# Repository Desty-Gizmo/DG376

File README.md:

# DG376

DG means "Desty Gizmo" or "Desty Gadget", a series of low power gadgets.

376: a random number I assign to name the model.

DG376V: using 10mm disk vibration motor (through-hole).
DG376R: using biased weight vibration motor (SMD).

# Counter

A counter that supports quick countdown function. Will notify the user when the time is up.

# MCU

STM32L010C6T6 $1.70 -> $1.67.  
STM32L011K4T6 $1.79 -> $1.68. Has symbol in KiCad

# Note

- Set GPIO to float before sleep.
-

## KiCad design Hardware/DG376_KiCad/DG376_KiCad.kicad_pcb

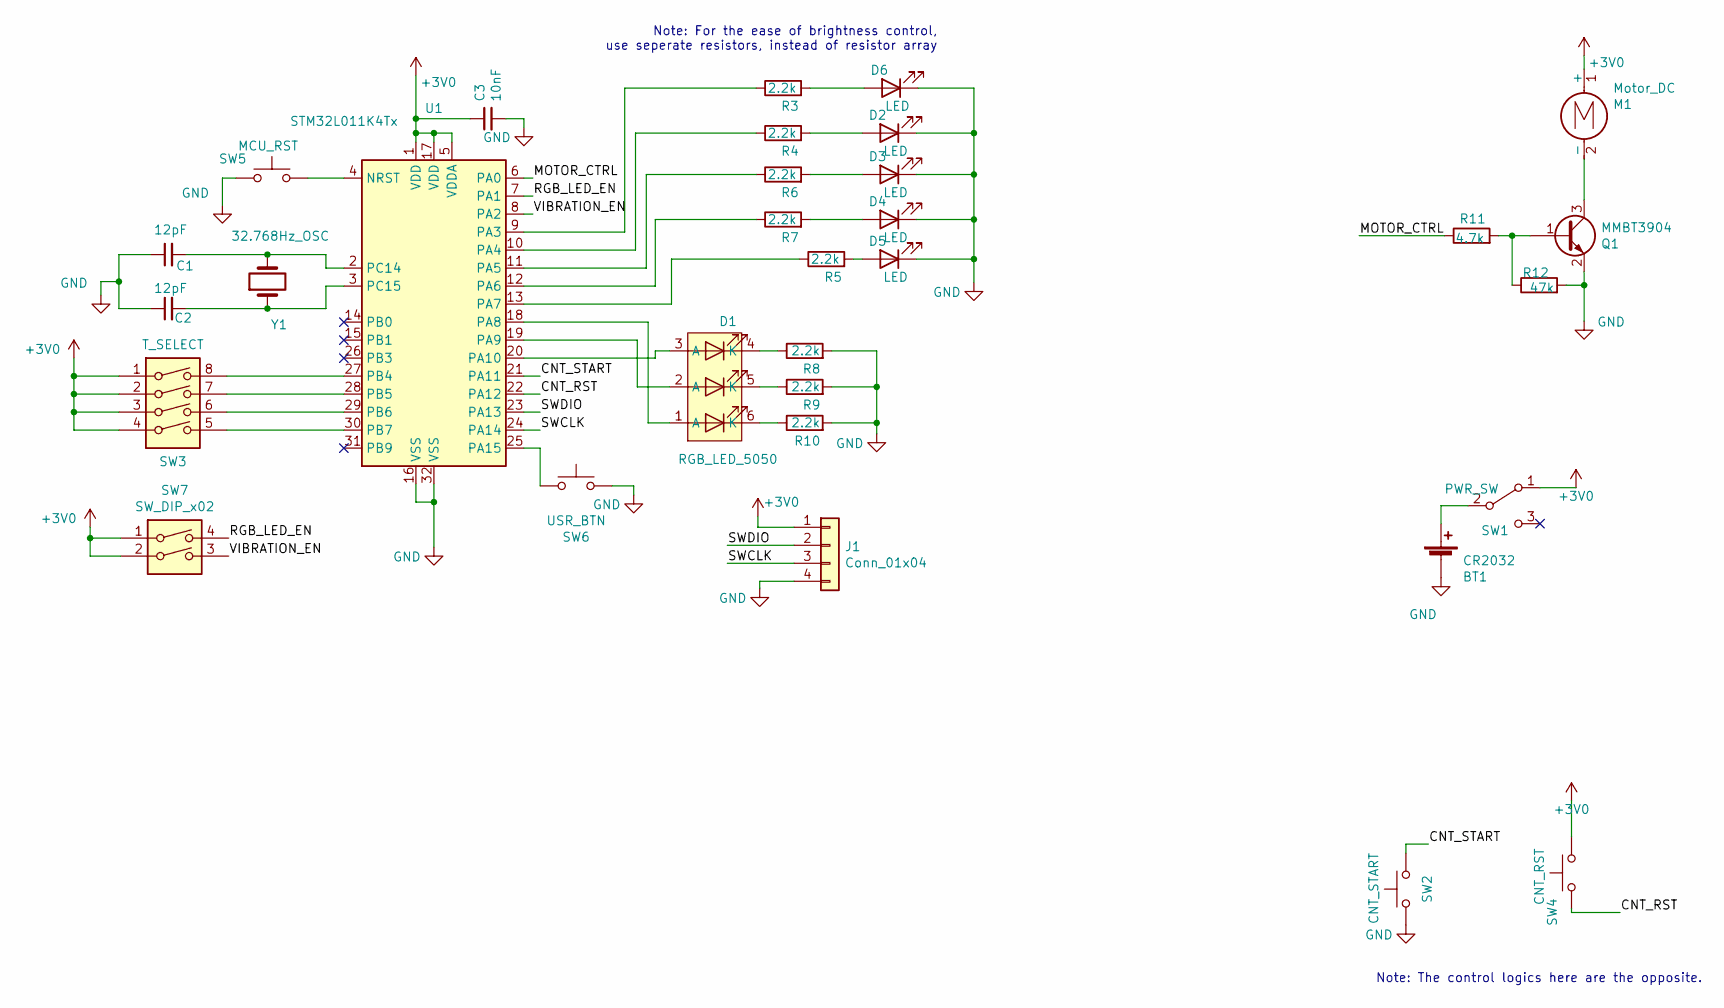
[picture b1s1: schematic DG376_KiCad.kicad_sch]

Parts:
BT1: CR2032; CR2032_Battery_Holder
C1, C2: 12pF; C_0603_1608Metric
C3: 10nF; C_0603_1608Metric
D1: RGB_LED_5050; LED_RGB_5050-6
D2, D3, D4, D5, D6: LED; LED_0603_1608Metric
J1: Conn_01x04; PinSocket_1x04_P1.27mm_Vertical
M1: Motor_DC; Vibration Motor 10mm
Q1: MMBT3904; SOT-23
R3, R4, R5, R6, R7, R8, R9, R10: 2.2k; R_0603_1608Metric
R11: 4.7k; R_0603_1608Metric
R12: 47k; R_0603_1608Metric
SW1: PWR_SW; Shouhan MSK12C02
SW2: CNT_START; Alps_SMD_Button_SKPMAPE010
SW3: T_SELECT; Diptronics DMR-04-V-TR
SW4: CNT_RST; Alps_SMD_Button_SKPMAPE010
SW5: MCU_RST; USAKRO UK-B0273-SP25Y
SW6: USR_BTN; USAKRO UK-B0273-SP25Y
SW7: SW_DIP_x02; Diptronics_SW_DIP_DHN-02-V-T-R
U1: STM32L011K4Tx; LQFP-32_7x7mm_P0.8mm
Y1: 32.768Hz_OSC; Crystal_SMD_3215-2Pin_3.2x1.5mm

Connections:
+3V0: C3.1, J1.1, M1.1 (+), SW1.1 (A), SW3.1, SW3.2, SW3.3, SW3.4, SW4.2, SW7.1, SW7.2, U1.1 (VDD), U1.5 (VDDA), U1.17 (VDD)
/CNT_RST: SW4.1, U1.22 (PA12)
/CNT_START: SW2.2, U1.21 (PA11)
/MOTOR_CTRL: R11.1, U1.6 (PA0)
/RGB_LED_EN: SW7.4, U1.7 (PA1)
/SWCLK: J1.3, U1.24 (PA14)
/SWDIO: J1.2, U1.23 (PA13)
/VIBRATION_EN: SW7.3, U1.8 (PA2)
GND: BT1.2 (-), C1.1, C2.1, C3.2, D2.1 (K), D3.1 (K), D4.1 (K), D5.1 (K), D6.1 (K), J1.4, Q1.2 (E), R8.2, R9.2, R10.2, R12.2, SW2.1, SW5.1, SW6.2, U1.16 (VSS), U1.32 (VSS)
unnamed: BT1.1 (+), SW1.2 (B)
unnamed: C1.2, U1.2 (PC14), Y1.2
unnamed: C2.2, U1.3 (PC15), Y1.1
unnamed: D1.1 (A), U1.18 (PA8)
unnamed: D1.2 (A), U1.19 (PA9)
unnamed: D1.3 (A), U1.20 (PA10)
unnamed: D1.4 (K), R8.1
unnamed: D1.5 (K), R9.1
unnamed: D1.6 (K), R10.1
unnamed: D2.2 (A), R4.2
unnamed: D3.2 (A), R6.2
unnamed: D4.2 (A), R7.2
unnamed: D5.2 (A), R5.2
unnamed: D6.2 (A), R3.2
unnamed: M1.2 (-), Q1.3 (C)
unnamed: Q1.1 (B), R11.2, R12.1
unnamed: R3.1, U1.9 (PA3)
unnamed: R4.1, U1.10 (PA4)
unnamed: R5.1, U1.13 (PA7)
unnamed: R6.1, U1.11 (PA5)
unnamed: R7.1, U1.12 (PA6)
unnamed: SW3.5, U1.30 (PB7)
unnamed: SW3.6, U1.29 (PB6)
unnamed: SW3.7, U1.28 (PB5)
unnamed: SW3.8, U1.27 (PB4)
unnamed: SW5.2, U1.4 (NRST)
unnamed: SW6.1, U1.25 (PA15)

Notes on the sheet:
Note: For the ease of brightness control, use seperate resistors, instead of resistor array
Note: The control logics here are the opposite.

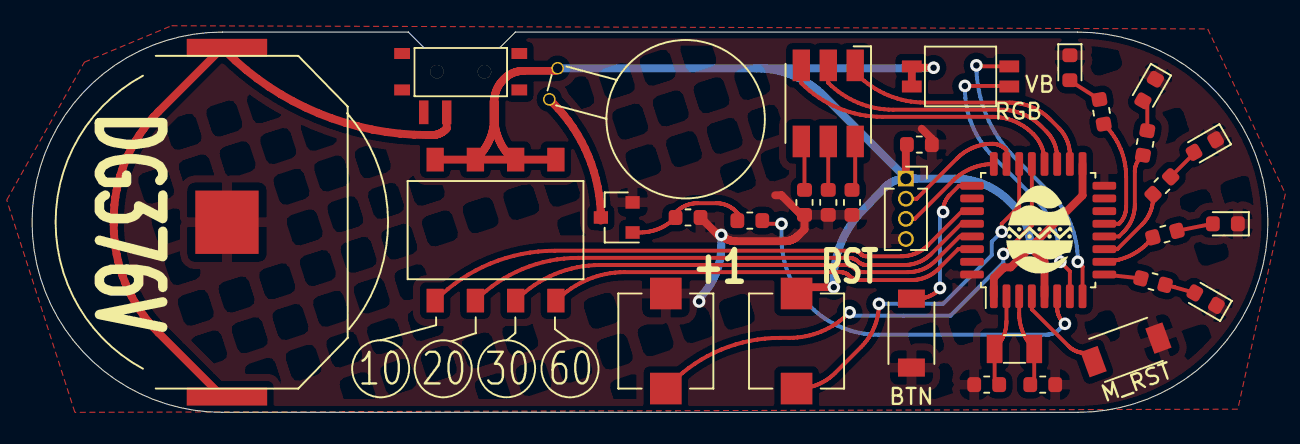
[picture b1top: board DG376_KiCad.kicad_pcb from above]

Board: 2 copper layers, 78.0 x 24.0 mm, 32 parts (0 on the bottom side), 36 nets.

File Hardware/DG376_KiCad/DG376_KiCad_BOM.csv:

"Source:","/Users/dlyang/Dropbox/Project/2020.DG376-Counter/Hardware/DG376_KiCad/DG376_KiCad.kicad_sch"
"Date:","Friday, June 05, 2020 at 02:58:03 PM"
"Tool:","Eeschema (5.99.0-1734-g575ad7128)"
"Generator:","/private/var/folders/nt/y2zl667d17z2_5mz2jj_qz8r0000gn/T/AppTranslocation/0FF80091-CBEB-471F-9E27-5001AB55A9E2/d/kicad.app/Contents/SharedSupport/plugins/bom_csv_grouped_by_value.py"
"Component Count:","32"

"Individual Components:"

"Item","Qty","Reference(s)","Value","LibPart","Footprint","Datasheet"
"","","BT1","CR2032","Device:Battery_Cell","LTD_Customized:CR2032_Battery_Holder","~"
"","","C1","12pF","Device:C_Small","Capacitor_SMD:C_0603_1608Metric","~"
"","","C2","12pF","Device:C_Small","Capacitor_SMD:C_0603_1608Metric","~"
"","","C3","10nF","Device:C_Small","Capacitor_SMD:C_0603_1608Metric","~"
"","","D1","RGB_LED_5050","DLY_Customized:RGB_LED_5050","LED_SMD:LED_RGB_5050-6",""
"","","D2","LED","Device:LED","LED_SMD:LED_0603_1608Metric","~"
"","","D3","LED","Device:LED","LED_SMD:LED_0603_1608Metric","~"
"","","D4","LED","Device:LED","LED_SMD:LED_0603_1608Metric","~"
"","","D5","LED","Device:LED","LED_SMD:LED_0603_1608Metric","~"
"","","D6","LED","Device:LED","LED_SMD:LED_0603_1608Metric","~"
"","","J1","Conn_01x04","Connector_Generic:Conn_01x04","Connector_PinSocket_1.27mm:PinSocket_1x04_P1.27mm_Vertical","~"
"","","M1","Motor_DC","Motor:Motor_DC","LTD_Customized:Vibration Motor 10mm","~"
"","","Q1","MMBT3904","Transistor_BJT:MMBT3904","Package_TO_SOT_SMD:SOT-23","https://www.fairchildsemi.com/datasheets/2N/2N3904.pdf"
"","","R3","2.2k","Device:R","Resistor_SMD:R_0603_1608Metric","~"
"","","R4","2.2k","Device:R","Resistor_SMD:R_0603_1608Metric","~"
"","","R5","2.2k","Device:R","Resistor_SMD:R_0603_1608Metric","~"
"","","R6","2.2k","Device:R","Resistor_SMD:R_0603_1608Metric","~"
"","","R7","2.2k","Device:R","Resistor_SMD:R_0603_1608Metric","~"
"","","R8","2.2k","Device:R","Resistor_SMD:R_0603_1608Metric","~"
"","","R9","2.2k","Device:R","Resistor_SMD:R_0603_1608Metric","~"
"","","R10","2.2k","Device:R","Resistor_SMD:R_0603_1608Metric","~"
"","","R11","4.7k","Device:R","Resistor_SMD:R_0603_1608Metric","~"
"","","R12","47k","Device:R","Resistor_SMD:R_0603_1608Metric","~"
"","","SW1","PWR_SW","Switch:SW_SPDT","LTD_Customized:Shouhan MSK12C02","~"
"","","SW2","CNT_START","Switch:SW_Push","LTD_Customized:Alps_SMD_Button_SKPMAPE010","~"
"","","SW3","T_SELECT","Switch:SW_DIP_x04","LTD_Customized:Diptronics DMR-04-V-TR","~"
"","","SW4","CNT_RST","Switch:SW_Push","LTD_Customized:Alps_SMD_Button_SKPMAPE010","~"
"","","SW5","MCU_RST","Switch:SW_Push","LTD_Customized:USAKRO UK-B0273-SP25Y","~"
"","","SW6","USR_BTN","Switch:SW_Push","LTD_Customized:USAKRO UK-B0273-SP25Y","~"
"","","SW7","SW_DIP_x02","Switch:SW_DIP_x02","LTD_Customized:Diptronics_SW_DIP_DHN-02-V-T-R","~"
"","","U1","STM32L011K4Tx","MCU_ST_STM32L0:STM32L011K4Tx","Package_QFP:LQFP-32_7x7mm_P0.8mm","http://www.st.com/st-web-ui/static/active/en/resource/techni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"
"","","Y1","32.768Hz_OSC","Device:Crystal","Crystal:Crystal_SMD_3215-2Pin_3.2x1.5mm","~"



"Collated Components:"

"Item","Qty","Reference(s)","Value","LibPart","Footprint","Datasheet"
"1","1","BT1","CR2032","Device:Battery_Cell","LTD_Customized:CR2032_Battery_Holder","~"
"2","2","C1, C2","12pF","Device:C_Small","Capacitor_SMD:C_0603_1608Metric","~"
"3","1","C3","10nF","Device:C_Small","Capacitor_SMD:C_0603_1608Metric","~"
"4","1","D1","RGB_LED_5050","DLY_Customized:RGB_LED_5050","LED_SMD:LED_RGB_5050-6",""
"5","5","D2, D3, D4, D5, D6","LED","Device:LED","LED_SMD:LED_0603_1608Metric","~"
"6","1","J1","Conn_01x04","Connector_Generic:Conn_01x04","Connector_PinSocket_1.27mm:PinSocket_1x04_P1.27mm_Vertical","~"
"7","1","M1","Motor_DC","Motor:Motor_DC","LTD_Customized:Vibration Motor 10mm","~"
"8","1","Q1","MMBT3904","Transistor_BJT:MMBT3904","Package_TO_SOT_SMD:SOT-23","https://www.fairchildsemi.com/datasheets/2N/2N3904.pdf"
"9","8","R3, R4, R5, R6, R7, R8, R9, R10","2.2k","Device:R","Resistor_SMD:R_0603_1608Metric","~"
"10","1","R11","4.7k","Device:R","Resistor_SMD:R_0603_1608Metric","~"
"11","1","R12","47k","Device:R","Resistor_SMD:R_0603_1608Metric","~"
"12","1","SW1","PWR_SW","Switch:SW_SPDT","LTD_Customized:Shouhan MSK12C02","~"
"13","1","SW2","CNT_START","Switch:SW_Push","LTD_Customized:Alps_SMD_Button_SKPMAPE010","~"
"14","1","SW3","T_SELECT","Switch:SW_DIP_x04","LTD_Customized:Diptronics DMR-04-V-TR","~"
"15","1","SW4","CNT_RST","Switch:SW_Push","LTD_Customized:Alps_SMD_Button_SKPMAPE010","~"
"16","1","SW5","MCU_RST","Switch:SW_Push","LTD_Customized:USAKRO UK-B0273-SP25Y","~"
"17","1","SW6","USR_BTN","Switch:SW_Push","LTD_Customized:USAKRO UK-B0273-SP25Y","~"
"18","1","SW7","SW_DIP_x02","Switch:SW_DIP_x02","LTD_Customized:Diptronics_SW_DIP_DHN-02-V-T-R","~"
"19","1","U1","STM32L011K4Tx","MCU_ST_STM32L0:STM32L011K4Tx","Package_QFP:LQFP-32_7x7mm_P0.8mm","http://www.st.com/st-web-ui/static/active/en/resource/techni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"
"20","1","Y1","32.768Hz_OSC","Device:Crystal","Crystal:Crystal_SMD_3215-2Pin_3.2x1.5mm","~"

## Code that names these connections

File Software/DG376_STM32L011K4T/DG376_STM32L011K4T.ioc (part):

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Mcu.Name=STM32L011K(3-4)Tx
Mcu.Package=LQFP32
Mcu.UserName=STM32L011K4Tx
PA0-CK_IN.GPIOParameters=GPIO_Label
PA0-CK_IN.GPIO_Label=MOTOR_CTRL
PA0-CK_IN.Signal=GPIO_Output
PA1.GPIOParameters=GPIO_PuPd,GPIO_Label
PA1.GPIO_Label=RGB_LED_EN
PA1.GPIO_PuPd=GPIO_PULLDOWN
PA1.Signal=GPIO_Input
PA10.GPIOParameters=GPIO_Label
PA10.GPIO_Label=LED_B
PA10.Signal=GPIO_Output
PA11.GPIOParameters=GPIO_PuPd,GPIO_Label,GPIO_ModeDefaultEXTI
PA11.GPIO_Label=CNT_START
PA11.GPIO_ModeDefaultEXTI=GPIO_MODE_IT_FALLING
PA11.GPIO_PuPd=GPIO_PULLUP
PA11.Signal=GPXTI11
PA12.GPIOParameters=GPIO_PuPd,GPIO_Label
PA12.GPIO_Label=CNT_RST
PA12.GPIO_PuPd=GPIO_PULLDOWN
PA12.Signal=GPXTI12
PA13.Mode=Serial_Wire
PA13.Signal=SYS_SWDIO
PA14.Mode=Serial_Wire
PA14.Signal=SYS_SWCLK
PA15.GPIOParameters=GPIO_PuPd,GPIO_Label
PA15.GPIO_Label=USR_BTN
PA15.GPIO_PuPd=GPIO_PULLUP
PA15.Signal=GPIO_Input
PA2.GPIOParameters=GPIO_PuPd,GPIO_Label
PA2.GPIO_Label=VIBRATION_EN
PA2.GPIO_PuPd=GPIO_PULLDOWN
PA2.Signal=GPIO_Input
PA3.GPIOParameters=GPIO_Label
PA3.GPIO_Label=LED_0
PA3.Signal=GPIO_Output
PA4.GPIOParameters=GPIO_Label
PA4.GPIO_Label=LED_1
PA4.Signal=GPIO_Output
PA5.GPIOParameters=GPIO_Label
PA5.GPIO_Label=LED_2
PA5.Signal=GPIO_Output
PA6.GPIOParameters=GPIO_Label
PA6.GPIO_Label=LED_3
PA6.Signal=GPIO_Output
PA7.GPIOParameters=GPIO_Label
PA7.GPIO_Label=LED_4
PA7.Signal=GPIO_Output
PA8.GPIOParameters=GPIO_Label
PA8.GPIO_Label=LED_R
PA8.Signal=GPIO_Output
PA9.GPIOParameters=GPIO_Label
PA9.GPIO_Label=LED_G
PA9.Signal=GPIO_Output
PB4.GPIOParameters=GPIO_PuPd,GPIO_Label
PB4.GPIO_Label=S_10_SELECT
PB4.GPIO_PuPd=GPIO_PULLDOWN
PB4.Signal=GPIO_Input
PB5.GPIOParameters=GPIO_PuPd,GPIO_Label
PB5.GPIO_Label=S_20_SELECT
PB5.GPIO_PuPd=GPIO_PULLDOWN
PB5.Signal=GPIO_Input
PB6.GPIOParameters=GPIO_PuPd,GPIO_Label
PB6.GPIO_Label=S_30_SELECT
PB6.GPIO_PuPd=GPIO_PULLDOWN
PB6.Signal=GPIO_Input
PB7.GPIOParameters=GPIO_PuPd,GPIO_Label
PB7.GPIO_Label=S_60_SELECT
PB7.GPIO_PuPd=GPIO_PULLDOWN
PB7.Signal=GPIO_Input
RCC.HSE_VALUE=8000000
RCC.SYSCLKFreq_VALUE=16000000
RCC.SYSCLKSource=RCC_SYSCLKSOURCE_HSI
board=custom
